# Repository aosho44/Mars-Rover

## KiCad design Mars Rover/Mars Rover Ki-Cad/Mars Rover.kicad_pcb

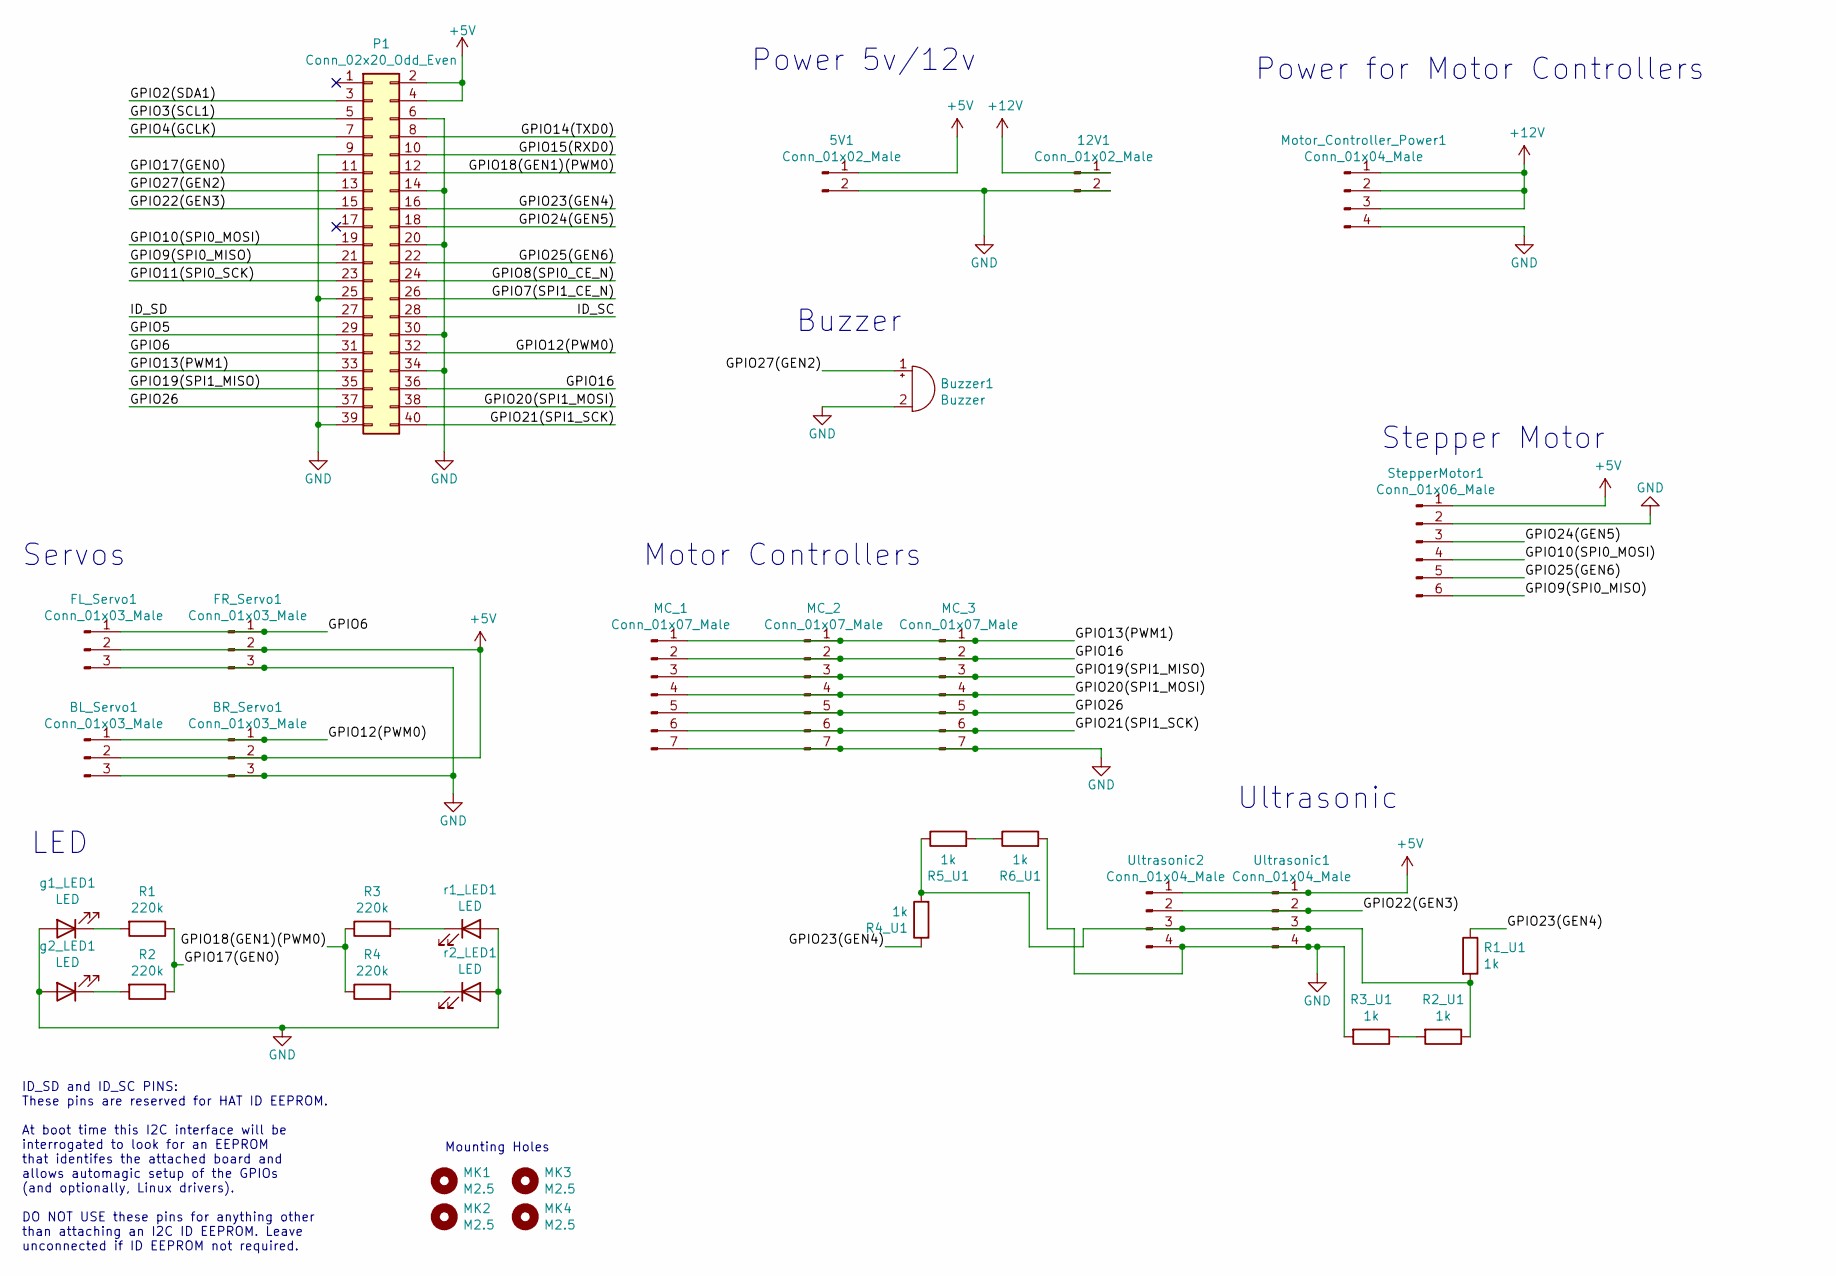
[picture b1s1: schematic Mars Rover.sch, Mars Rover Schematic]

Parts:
5V1, 12V1: Conn_01x02_Male; PinHeader_1x02_P2.54mm_Vertical
BL_Servo1: Conn_01x03_Male; PinHeader_1x03_P2.54mm_Vertical
BR_Servo1: Conn_01x03_Male; PinHeader_1x03_P2.54mm_Vertical
Buzzer1: Buzzer; Buzzer_12x9.5RM7.6
FL_Servo1: Conn_01x03_Male; PinHeader_1x03_P2.54mm_Vertical
FR_Servo1: Conn_01x03_Male; PinHeader_1x03_P2.54mm_Vertical
MC_1, MC_2, MC_3: Conn_01x07_Male; PinHeader_1x07_P2.54mm_Vertical
MK1, MK2, MK3, MK4: M2.5; MountingHole_2.7mm_M2.5
Motor_Controller_Power1: Conn_01x04_Male; PinHeader_1x04_P2.54mm_Vertical
P1: Conn_02x20_Odd_Even; PinSocket_2x20_P2.54mm_Vertical
R1, R2, R3, R4: 220k; R_Axial_DIN0207_L6.3mm_D2.5mm_P7.62mm_Horizontal
R1_U1, R2_U1, R3_U1, R4_U1, R5_U1, R6_U1: 1k; R_Axial_DIN0207_L6.3mm_D2.5mm_P7.62mm_Horizontal
StepperMotor1: Conn_01x06_Male; PinHeader_1x06_P2.54mm_Vertical
Ultrasonic1, Ultrasonic2: Conn_01x04_Male; PinHeader_1x04_P2.54mm_Vertical
g1_LED1, g2_LED1: LED; LED_D3.0mm_Clear
r1_LED1, r2_LED1: LED; LED_D3.0mm_Clear

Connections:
+5V: 5V1.1, BL_Servo1.2, BR_Servo1.2, FL_Servo1.2, FR_Servo1.2, P1.2, P1.4, StepperMotor1.1, Ultrasonic1.1, Ultrasonic2.1
+12V: 12V1.1, Motor_Controller_Power1.1, Motor_Controller_Power1.2, Motor_Controller_Power1.3
/GPIO2(SDA1): P1.3
/GPIO3(SCL1): P1.5
/GPIO4(GCLK): P1.7
/GPIO5: P1.29
/GPIO6: FL_Servo1.1, FR_Servo1.1, P1.31
/GPIO7(SPI1_CE_N): P1.26
/GPIO8(SPI0_CE_N): P1.24
/GPIO9(SPI0_MISO): P1.21, StepperMotor1.6
/GPIO10(SPI0_MOSI): P1.19, StepperMotor1.4
/GPIO11(SPI0_SCK): P1.23
/GPIO12(PWM0): BL_Servo1.1, BR_Servo1.1, P1.32
/GPIO13(PWM1): MC_1.1, MC_2.1, MC_3.1, P1.33
/GPIO14(TXD0): P1.8
/GPIO15(RXD0): P1.10
/GPIO16: MC_1.2, MC_2.2, MC_3.2, P1.36
/GPIO17(GEN0): P1.11, R1.1, R2.1
/GPIO18(GEN1)(PWM0): P1.12, R3.1, R4.1
/GPIO19(SPI1_MISO): MC_1.3, MC_2.3, MC_3.3, P1.35
/GPIO20(SPI1_MOSI): MC_1.4, MC_2.4, MC_3.4, P1.38
/GPIO21(SPI1_SCK): MC_1.6, MC_2.6, MC_3.6, P1.40
/GPIO22(GEN3): P1.15, Ultrasonic1.2, Ultrasonic2.2
/GPIO23(GEN4): P1.16, R1_U1.1, R4_U1.1
/GPIO24(GEN5): P1.18, StepperMotor1.3
/GPIO25(GEN6): P1.22, StepperMotor1.5
/GPIO26: MC_1.5, MC_2.5, MC_3.5, P1.37
/GPIO27(GEN2): Buzzer1.1 (-), P1.13
/ID_SC: P1.28
/ID_SD: P1.27
GND: 5V1.2, 12V1.2, BL_Servo1.3, BR_Servo1.3, Buzzer1.2 (+), FL_Servo1.3, FR_Servo1.3, MC_1.7, MC_2.7, MC_3.7, Motor_Controller_Power1.4, P1.6, P1.9, P1.14, P1.20, P1.25, P1.30, P1.34, P1.39, R3_U1.2, R6_U1.2, StepperMotor1.2, Ultrasonic1.4, Ultrasonic2.4, g1_LED1.2 (A), g2_LED1.2 (A), r1_LED1.2 (A), r2_LED1.2 (A)
unnamed: R1.2, g1_LED1.1 (K)
unnamed: R1_U1.2, R2_U1.1, R4_U1.2, R5_U1.1, Ultrasonic1.3, Ultrasonic2.3
unnamed: R2.2, g2_LED1.1 (K)
unnamed: R2_U1.2, R3_U1.1
unnamed: R3.2, r1_LED1.1 (K)
unnamed: R4.2, r2_LED1.1 (K)
unnamed: R5_U1.2, R6_U1.1

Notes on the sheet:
Mounting Holes
Servos
Power 5v/12v
LED
ID_SD and ID_SC PINS: These pins are reserved for HAT ID EEPROM. At boot time this I2C interface will be interrogated to look for an EEPROM that identifes the attached board and allows automagic setup of the GPIOs (and optionally, Linux drivers). DO NOT USE these pins for anything other than attach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
Motor Controllers
Buzzer
Stepper Motor
Ultrasonic
Power for Motor Controllers

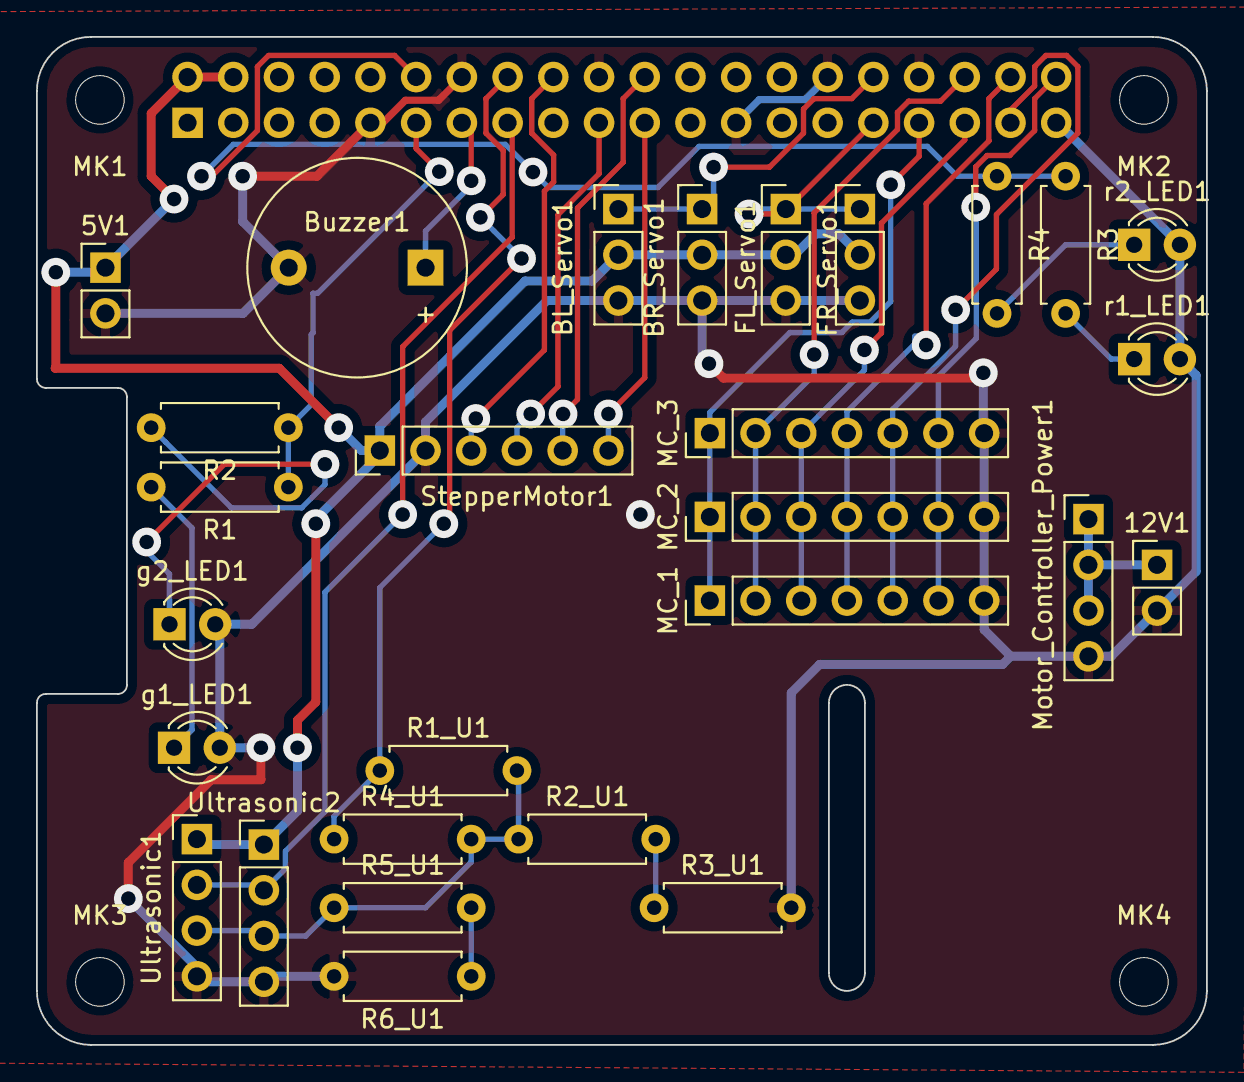
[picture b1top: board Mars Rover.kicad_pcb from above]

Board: 2 copper layers, 65.0 x 56.0 mm, 33 parts (1 on the bottom side), 27 nets.
